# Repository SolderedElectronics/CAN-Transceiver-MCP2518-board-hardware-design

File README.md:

# CAN Transceiver MCP2518 board Hardware Design

## About the Product

|  |
| :----------------------------------------------------------: |
| [Buy CAN Transceiver MCP2518 board](https://www.solde.red/333020) |

CAN Transceiver (Controller Area Network) is a network technology that enables fast communication between microcontrollers, and is the most commonly used standard in cars. Our CAN breakout uses an MCP2518FD CAN whose communication between microcontrollers takes place on SPI protocol. In addition there is a CAN transceiver. This breakout allows use of both standards (CAN 2.0B and CAN Flexible Data (FD)). Access to the CAN bus is possible via CANH and CANL pins on the screw terminal. The 120ohm terminator resistor is also located on the board and can be connected to a jumper.

---

## Repository Contents

This repository contains all design files for CAN Transceiver MCP2518 board, organized as follows:

- **`CAD` folder**: Contains KiCAD design files, including:
  - Schematics
  - PCB layout
  - Panel PCB layout
  - Source 3D files in Fusion360, if any
  - All files are sorted by version with a detailed change log.
- **`OUTPUTS` folder**: Includes all production-ready files, such as:
  - Bill of Materials (BOM) and interactive BOM (iBOM)
  - PDF versions of schematics
  - 3D `.step` file of the board
  - 3D-printable models
  - Gerber files for PCB manufacturing
  - Image of the pinout of the board
  - Product image
  - Compliance, legal and generic sales documents

Refer to the `Change Log` in the CAD folder for details about updates between versions.

---

## Learn More About the Product

Beyond the repository, explore the following resources:

### Soldered Verify

The **Soldered Verify** system ensures every board you purchase from Soldered is fully functional. It also provides access to exclusive test data for your product. To get started, find the unique Soldered Verify ID on your product's packaging and enter the ID on the [Soldered Verify page](https://soldered.com/verify/) to access test results and additional product details.

### Soldered Community

Soldered Community is your go-to place for technical support. Our engineers track and answer all questions posted there, and it’s a great space for the maker community. Get answers to your questions and solutions for your challenges at [Soldered Community](https://soldered.com/community).

### solde.red

solde.red is an ultimate URL shortener and information hub. Access it by typing solde.red/ followed by your product SKU, e.g., [solde.red/333000](https://solde.red/333000), to find getting-started guides, datasheets, open-source hardware and software files, certifications, images, pinouts, and more. Read more about the shortener [here](https://solde.red/info/).

---

## Contributing

Contributions are welcome! Here’s how you can get involved:

- Submit pull requests to enhance the design or fix issues.
- Report bugs or problems by opening an issue.

We encourage community collaboration to make this product even better.

---

## About Soldered

[Soldered for Makers](https://soldered.com) specializes in designing and manufacturing electronic products tailored for enthusiasts, ranging from hobbyists to professionals. Our portfolio includes electronic boards, sensors, and actuators that are widely utilized in fields such as microelectronics, mechatronics, robotics, programming, and IoT. Every product we offer is designed in-house and built upon open-source hardware and software platforms. Proudly certified and manufactured within the European Union, our catalog likely includes the product you need for your project.

We complement these products with comprehensive tutorials and manuals, product descriptions, schematics, programming codes, and project examples. Our round-the-clock [customer and technical support](https://soldered.com/community) is available for all our products, irrespective of the sales channel. Soldered’s success and services reflect our maker community’s unwavering [trust](https://www.trustpilot.com/review/soldered.com), for which we are deeply grateful. Join our community and create using Soldered products.

---

## License

All Soldered open-source hardware (OSH) is under The TAPR Open Hardware License. Read more in the LICENSE file located in this repository.

**Disclaimer:**

No warranty - all designs in this repository are distributed in the hope that they will be useful, but without any warranty. They are provided "AS IS", therefore without warranty of any kind, either expressed or implied. The entire quality and performance of what you do with the contents of this repository are your responsibility. In no event Soldered Electronics will be liable for your damages, or losses, including any general, special, incidental, or consequential damage arising out of the use or inability to use the contents of this repository. 

---

## Have fun!

Thank you for your support from your fellow makers at Soldered Electronics.

Happy Making!

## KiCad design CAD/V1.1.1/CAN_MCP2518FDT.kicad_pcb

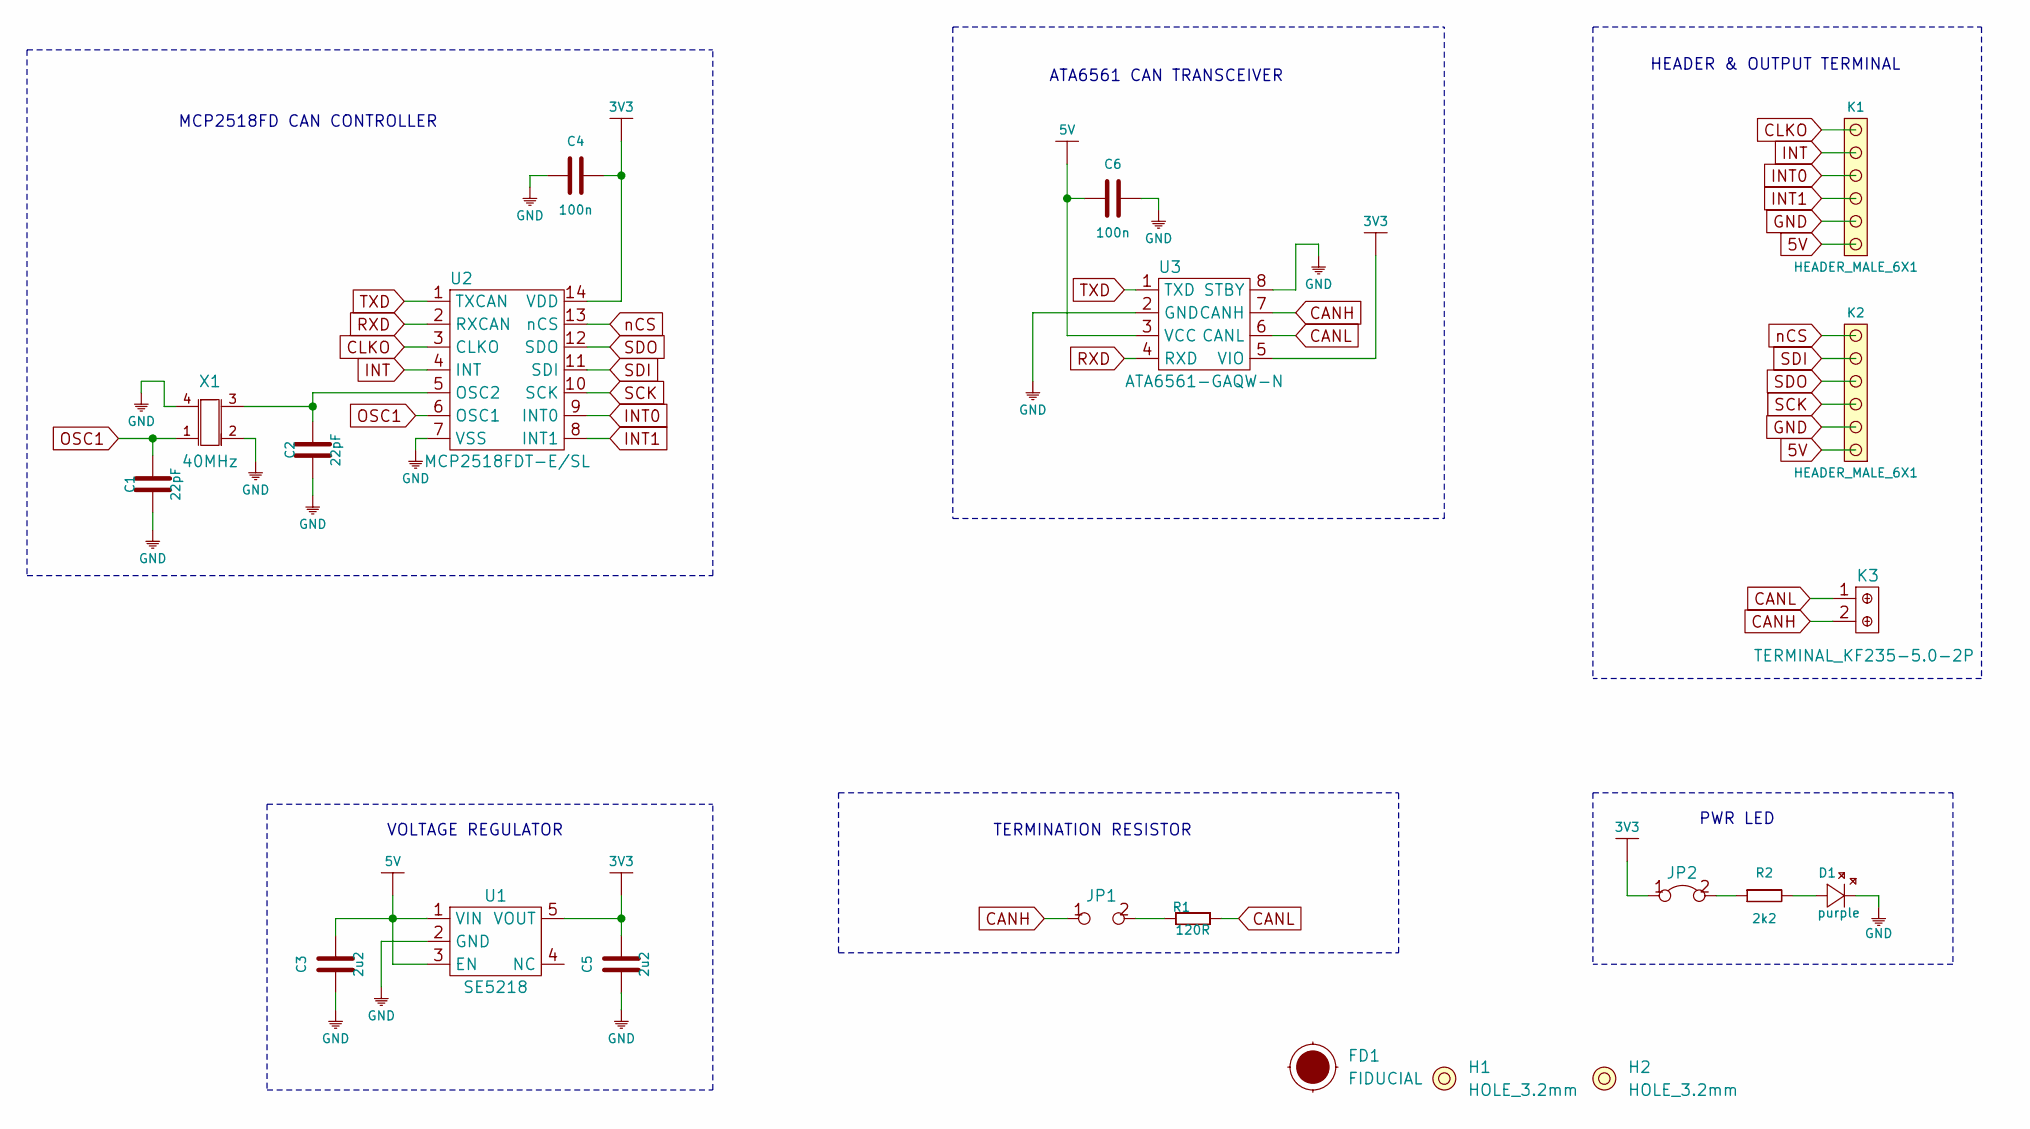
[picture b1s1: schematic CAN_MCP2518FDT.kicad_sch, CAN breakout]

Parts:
C1, C2: 22pF; 0603C
C3, C5: 2u2; 0603C
C4, C6: 100n; 0603C
D1: purple; 0402LED
FD1: FIDUCIAL; FIDUCIAL_23
H1, H2: HOLE_3.2mm
JP1: SMD_JUMPER
JP2: SMD-JUMPER-CONNECTED_TRACE_SLODERMASK
K1, K2: HEADER_MALE_6X1
K3: TERMINAL_KF235-5.0-2P
R1: 120R; 0603R
R2: 2k2; 0402R
U1: SE5218; SOT-23-5
U2: MCP2518FDT-E/SL; SOIC-14
U3: ATA6561-GAQW-N; SOIC−8
X1: 40MHz; KRISTAL_3225__4_PAD

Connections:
3V3: C4.2, C5.2, JP2.1, U1.5 (VOUT), U2.14 (VDD), U3.5 (VIO)
5V: C3.2, C6.1, K1.1, K2.1, U1.1 (VIN), U1.3 (EN), U3.3 (VCC)
CANH: JP1.1, K3.2, U3.7 (CANH)
CANL: K3.1, R1.2, U3.6 (CANL)
CLKO: K1.6, U2.3 (CLKO)
GND: C1.1, C2.1, C3.1, C4.1, C5.1, C6.2, D1.2 (K), K1.2, K2.2, U1.2 (GND), U2.7 (VSS), U3.2 (GND), U3.8 (STBY), X1.2, X1.4
INT: K1.5, U2.4 (INT)
INT0: K1.4, U2.9 (INT0)
INT1: K1.3, U2.8 (INT1)
unnamed: C2.2, U2.5 (OSC2), X1.3
unnamed: D1.1 (A), R2.2
unnamed: JP1.2, R1.1
unnamed: JP2.2, R2.1
OSC1: C1.2, U2.6 (OSC1), X1.1
RXD: U2.2 (RXCAN), U3.4 (RXD)
SCK: K2.3, U2.10 (SCK)
SDI: K2.5, U2.11 (SDI)
SDO: K2.4, U2.12 (SDO)
TXD: U2.1 (TXCAN), U3.1 (TXD)
nCS: K2.6, U2.13 (nCS)

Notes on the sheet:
HEADER & OUTPUT TERMINAL
TERMINATION RESISTOR
PWR LED
VOLTAGE REGULATOR
ATA6561 CAN TRANSCEIVER
MCP2518FD CAN CONTROLLER

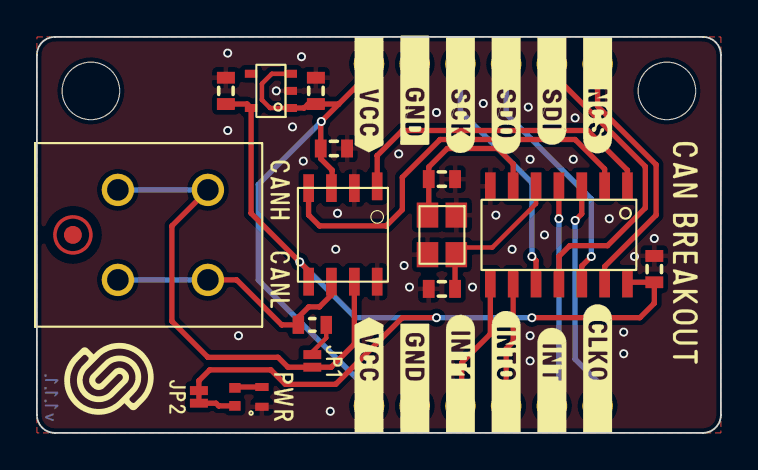
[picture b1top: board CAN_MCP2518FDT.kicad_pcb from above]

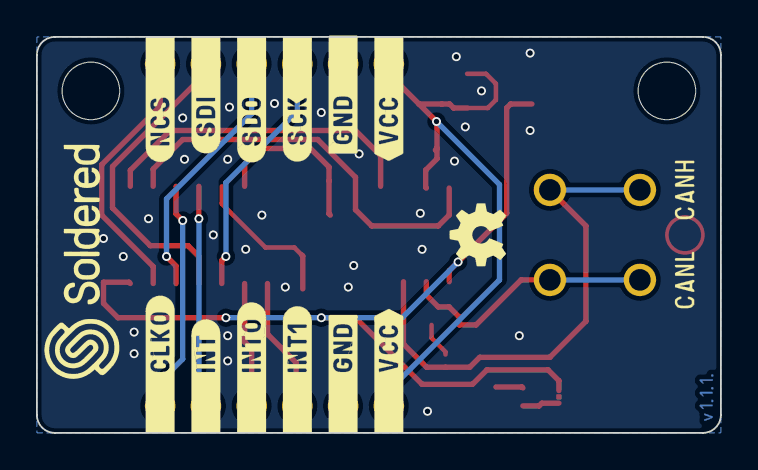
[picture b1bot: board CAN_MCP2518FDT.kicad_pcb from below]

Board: 2 copper layers, 38.0 x 22.0 mm, 21 parts (2 on the bottom side), 20 nets.

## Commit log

2022-08-06 Updating open source files.
